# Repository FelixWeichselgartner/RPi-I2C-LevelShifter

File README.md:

Raspberry Pi I²C Level-Shifter
==============================

A PiHAT for converting the Raspberry Pi I²C Signals from 3.3V levels to 5V levels, which is usefull if you want to interface with I²C-components that use 5V voltage levels. The project aims to save time in wiring up an external level-shifter and just plug a shield on top of the gpio pins of the Raspberry Pi.

## Schematics, Layout

<br>

<br>

## Application

This is how the module is supposed to be used:

On Raspberry Pi 3B+:

<br>

On Raspberry Pi Compute Module 4 IO Board:

<br>

## Testing

I tested the pcb, however I hand-soldered everything (which I can definitely not recommend). Everything is soldered exactly like in the schematic, even though I placed some parts differently.

Here is how my prototype looks like:

<br>

<br>
And here are my oscilloscope measurements on level shifting a rectangular pulse with the following frequencies:

40kHz:

<br>

200kHz:

<br>

500kHz (from here on it doesn't seem to be able to reach the full 5V):

<br>

This behaviours is confirmed by simulation.

And here a screenshot of the included LT-Spice simulation:

<br>

And here a simulation of high frequencies. This shows (as the real graph above) that the mosfet is too slow for MHz frequencies. Replace the mosfet with a faster one if you have to a high frequency application.

<br>

## Dependencies

2N7002 MOSFET library (lbr/transistors_gaui.lbr):
* http://eagle.autodesk.com/eagle/download/1129

## License

The project is licensed under the MIT-License. For further information see `LICENSE.md`.

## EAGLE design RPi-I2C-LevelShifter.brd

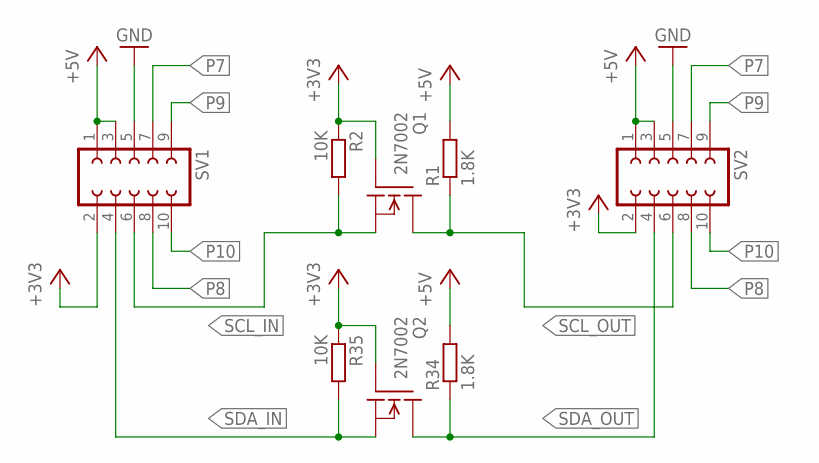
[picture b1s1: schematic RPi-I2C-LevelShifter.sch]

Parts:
Q1, Q2: 2N7002; SOT23
R1, R34: 1.8K; R0805
R2, R35: 10K; R0805
SV1, SV2: FE05-2

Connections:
+3V3: Q1.1 (G), Q2.1 (G), R2.1, R35.1, SV1.2, SV2.2
+5V: R1.2, R34.2, SV1.1, SV1.3, SV2.1, SV2.3
GND: SV1.5, SV2.5
P7: SV1.7, SV2.7
P8: SV1.8, SV2.8
P9: SV1.9, SV2.9
P10: SV1.10, SV2.10
SCL_IN: Q1.2 (S), R2.2, SV1.6
SCL_OUT: Q1.3 (D), R1.1, SV2.6
SDA_IN: Q2.2 (S), R35.2, SV1.4
SDA_OUT: Q2.3 (D), R34.1, SV2.4

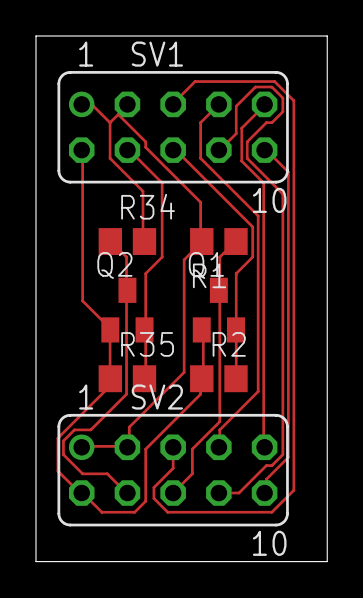
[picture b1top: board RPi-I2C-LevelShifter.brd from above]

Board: 2 copper layers, 16.2 x 29.2 mm, 8 parts (0 on the bottom side), 11 nets.

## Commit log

2021-04-14 fixed error
2021-04-14 optimized layout
2021-04-17 added simulation; improved layout
2021-04-17 finished and tested.
2021-04-17 fixed readme
2021-04-20 fixed typo
2021-04-20 explain high freq behaviour
2021-04-20 fix readme
2021-05-27 made freq variable; better simulation image
